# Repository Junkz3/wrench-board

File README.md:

<p align="center">
  <strong>English</strong> ·
  <a href="README.fr.md">Français</a> ·
  <a href="README.zh.md">中文</a> ·
  <a href="README.hi.md">हिन्दी</a> ·
  <a href="README.pt-BR.md">Português</a>
</p>

# Wrench Board

<p align="center">

</p>

> Agent-native diagnostic workbench for board-level electronics repair,
> powered by Claude Opus 4.8. **Right-to-repair, built in the open, by the
> people who actually do the repairs.**

🥈 **2nd place** at Anthropic's *Build with Opus 4.7* hackathon, April 2026.

**📺 Demo video (3 min):** https://youtu.be/OZ2D_p82z6w

**Try it online:** [open a boardview in the browser, free](https://wrenchboard.cloud/boardview-viewer). No account, no install: `.brd`, `.fz`, `.tvw`, `.pcb` and more, parsed natively.

## What it is

Tens of millions of tonnes of electronics end up as e-waste every year. A
large share of that is recoverable at the board level: a dead capacitor, a
blown diode, a bad PMIC, but only a microsoldering technician can find and
fix it. We are the **last mile** of repair before the landfill, and there
are not many of us.

Wrench Board is a senior microsoldering teammate built for that last mile.
For the seasoned tech, it's a second pair of eyes that never gets tired.
For the apprentice, it's a senior teammate who explains the boot sequence
the tenth time, in their language, with their tools, without judgment. It ingests a schematic PDF and a
boardview, builds a per-device knowledge pack in two minutes, and runs an
Opus 4.8 diagnostic agent that pilots the board visually (highlights
pins, traces nets, simulates failures) while the technician keeps the
iron in their hand.

It is device-agnostic. Feed it a schematic and a boardview and it works
the same on iPhone and MacBook logic boards, Android and Samsung phones,
game console motherboards, laptops, and single-board computers. Anything
with a schematic and a boardview is fair game.

The bet is **precision over magic**. The agent is not allowed to invent a
reference designator. Every refdes it utters originates from a tool lookup,
and a server-side sanitizer wraps any token it cannot verify *before* the
text reaches the screen. The deterministic engines underneath produce
verifiable causal chains, not vibes.

## Why it exists

I've been a microsoldering technician for three years. For most of that
time, I sent screenshots to Claude one at a time, manually, and pasted the
answer into a paper notebook. I built the workbench I needed.

## How it works

Four orthogonal workflows feed a single on-disk corpus per device under
`memory/{slug}/`:

- **Knowledge Factory**: four Claude personas (Scout, Registry, Writers,
  Auditor) build a verified repair pack from a device label in ~2 minutes.
  The three Writers (Cartographe / Clinicien / Lexicographe) run in
  parallel and share a cache-warmed prefix to amortize the long shared
  input across writers.
- **Schematic Ingestion**: Opus 4.8 vision compiles a PDF schematic, page
  by page, into a queryable `ElectricalGraph`: nets classified, boot
  sequence inferred, quality report attached.
- **Diagnostic Agent**: an Anthropic Managed Agent per device, with a
  four-store layered memory (`global-patterns`, `global-playbooks`,
  `device-{slug}`, `repair-{repair_id}`), pilots the boardview through 17
  `bv_*` tools and queries the pack, schematic graph, measurements,
  validations and technician profile through 27 more: 44 custom tools
  declared in `api/agent/manifest.py`. The agent never fabricates a
  refdes: tool discipline plus a post-hoc sanitizer.
- **microsolder-evolve**: four overnight search loops, one
  per surface: the deterministic simulator + hypothesize engines
  (`sim`), the schematic compiler (`pipeline`), the schematic vision
  pass (`pipeline-vision`), and the diagnostic agent itself (`agent`).
  Each loop proposes patches against an oracle benchmark and either
  keeps them (`evolve:`-prefixed commit) or reverts. The loops have
  been running and shipping improvements while I work on other things.

### Files + Vision: the agent can ask to see

A microsoldering diagnosis lives or dies on what the probe is touching
*right now*, and a chat box can't carry that. The technician plugs a USB
microscope or webcam into the workbench and the agent requests a frame on
demand through the `cam_capture` tool, reads the image, and feeds it back
into its reasoning. The technician can also drop a macro shot or a close-up
of a suspect chip into the chat at any time. Captures and uploads are
persisted under the repair so a session can be replayed end-to-end:
words, decisions, and the actual photographs the agent looked at.

This closes the loop the screenshot-pasting workflow never could: the
agent stops *guessing* what the board looks like and starts *seeing* it,
on the technician's cue, on the technician's optics.

## Under the hood

- **Backend**: Python 3.11+ / FastAPI / native WebSocket / Pydantic v2 /
  pdfplumber. No build step, no bundler.
- **Frontend**: vanilla HTML + CSS + JS, OKLCH design tokens, D3 v7 for the
  knowledge graph and Three.js r128 (WebGL) for the boardview. Inline SVG
  icons. No framework.
- **Models**: Claude Opus 4.8 (heavy pipeline writers, schematic vision,
  `deep` diagnostic tier), Claude Sonnet 4.6 (Scout, Registry, Mapper,
  Lexicographe, `normal` tier), Claude Haiku 4.5 (intent classifier, phase
  narrator, coverage gate, `fast` tier).
- **Memory**: per-device Anthropic Managed Agents memory stores. The
  agent self-orients across sessions by reading its own scribe notebook
  (`state.md`, `decisions/`, `measurements/`, `open_questions.md`)
  instead of relying on an LLM-generated resume.
- **Boardview**: 16 parsers in `api/board/parser/`, dispatched
  by extension: KiCad `.kicad_pcb`, OpenBoardView Test_Link `.brd`,
  KiCad-boardview BRD2, plus `.asc` `.bdv` `.bv` `.bvr` `.cad` `.cst`
  `.f2b` `.fz` `.gr` `.pcb` `.tvw`. Adding a format = one new file.
- **Tests**: 2 600+ fast tests (~1 min) plus a `@slow` accuracy-gate suite,
  including 10 deterministic invariants on the simulator + hypothesize
  engines and frozen-oracle gates.
- **Tooling**: `make doctor` runs 8 local health checks (env, packs,
  parsers, camera) for atelier deployment. `make eval-all` orchestrates
  the four eval surfaces (simulator, pipeline, vision, agent) with
  cross-skill regression detection. `make tools-inventory` writes a
  local agent-manifest index for offline review.
- **Anti-hallucination**: defense in depth, two layers. (1) Tools return
  `{found: false, closest_matches: [...]}` for unknown refdes; the system
  prompt instructs the agent to pick from suggestions or ask the user.
  (2) `api/agent/sanitize.py` scans every outbound text for refdes-shaped
  tokens (`\b[A-Z]{1,3}\d{1,4}\b`) and wraps any unverified match as
  `⟨?U999⟩` before it reaches the technician.

Two pure-sync deterministic engines (`simulator.py`, `hypothesize.py`) sit
at the core of the diagnostic stack. The simulator advances phase-by-phase
over a boot sequence and emits a timeline of dead rails, dead components,
and the cause of blocking per phase. The hypothesizer takes a partial
observation and enumerates 1- and 2-fault refdes-kill candidates that
explain it, ranked by F1 against the observation. Neither calls an LLM at
runtime.

The diagnostic agent has two interchangeable runtimes: **managed** via
Anthropic Managed Agents, **direct** via the Messages API. Managed is the
default and the production path; direct serves as a fallback when the MA
beta is unavailable and as an on-disk inspection harness during
development. The WebSocket protocol is identical so the frontend doesn't
know which one is running.

## Roadmap: Community Evolution Loop

Wrench Board runs locally. Each technician's instance can improve its
deterministic simulator against their own field cases. When the evolve
loop discovers a rule that holds up, it surfaces a candidate pull request
to the upstream repo. Right-to-repair, built in the open, by the people
who actually do the repairs.

## Quickstart

```bash
git clone https://github.com/Junkz3/wrench-board
cd wrench-board
make install          # create .venv and install deps (incl. [dev])
cp .env.example .env  # then fill in ANTHROPIC_API_KEY
make run              # uvicorn --reload on http://localhost:8000
```

On the first `make run` in Managed Agents mode (default), the start
script prints a one-screen warning describing what it is about to create
on your Anthropic account (1 environment + 3 tier-scoped agents, idle,
no cost until used) and waits 5 seconds for Ctrl+C before bootstrapping.
The IDs land in `managed_ids.json` (gitignored) and subsequent runs go
straight to uvicorn.

Fallback to direct mode if the Managed Agents beta is unavailable on
your account, no bootstrap, plain `messages.create` tool loop:

```bash
make demo-fallback
# or: DIAGNOSTIC_MODE=direct make run
```

## License & credits

Source-available under a proprietary license. See [`LICENSE`](LICENSE).
Free for personal evaluation, study, and local use. **Independent
electronics repair professionals may also use it as an internal tool
when servicing their own clients** (commercial remuneration OK), with
no separate licence needed. Redistribution, hosted SaaS deployment,
sublicensing, and any use for training competing AI / ML models still
require written permission (contact: alexis@repairmind.co.uk).
Dependencies are MIT / Apache 2.0 / BSD only. The MNT Reform motherboard
used as the canonical test target is CERN-OHL-S-2.0. Built solo at
Repair Valley, an independent electronics repair workshop.

## Contributing

Wrench Board is open to contributors who care about right-to-repair.
Field reports, new boardview parsers, simulator rules: open an issue or
a PR.

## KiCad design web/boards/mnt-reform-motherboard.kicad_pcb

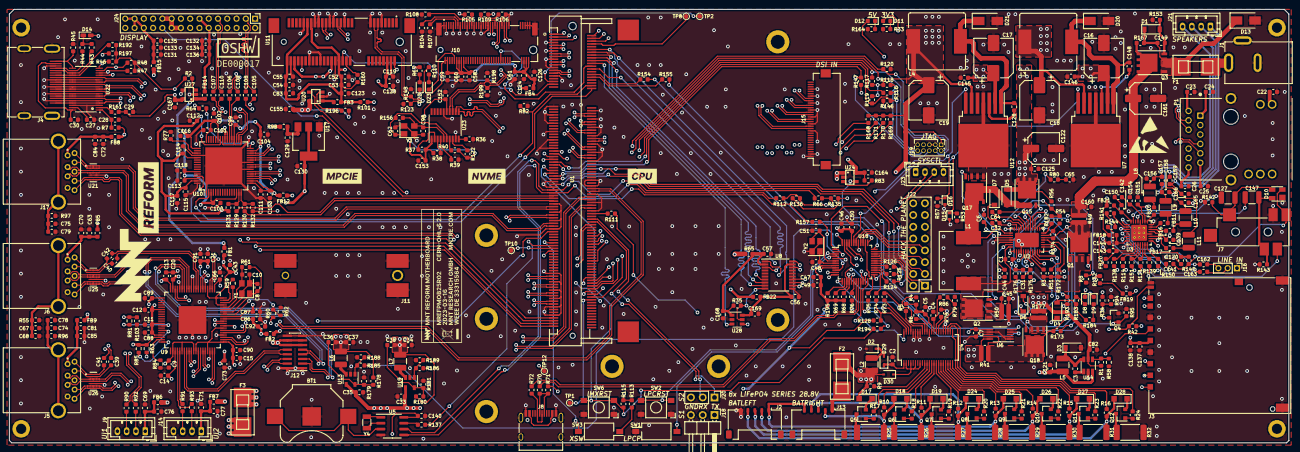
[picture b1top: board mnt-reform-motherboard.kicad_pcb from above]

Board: 6 copper layers, 276.0 x 93.5 mm, 505 parts (0 on the bottom side), 450 nets.

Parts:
BT1: CR1220; BatteryHolder_Keystone_3000_1x12mm
C1, C4, C5, C32, C73, C87, C89, C100, C111, C114, C129, C130, C141, C145, C146, C162, C163: 1uF; C_0603_1608Metric
C2, C7, C9, C11, C12, C13, C14, C15, C20, C21, C22, C23, C24, C25, C26, C27, C28, C29, C30, C39, C40, C41, C42, C43, C49, C50, C53, C54, C55, C56, C57, C59, C60, C61, C66, C67, C70, C74, C75, C76, C77, C84, C85, C86, C88, C90, C101, C103, C105, C106, C107, C108, C109, C110, C113, C115, C118, C119, C135, C136, C138, C140, C142, C143, C144, C149, C154, C156, C158, C165, C166, C168, C169: 0.1uF; C_0603_1608Metric
C3, C31: 0.33uF; C_0603_1608Metric
C6, C33, C35, C139, C151, C170: 4.7uF; C_0603_1608Metric
C8, C10, C48, C51, C62, C98: 18pF; C_0603_1608Metric
C16, C17: 100uF; CP_Elec_8x10
C18, C19: 220uF; CP_Elec_8x10
C34, C37, C46, C47, C63, C69, C71, C72, C81, C91, C92, C99, C112, C120, C131, C132, C133, C134, C137, C150, C155, C164, C167: 10uF; C_0603_1608Metric
C36, C38: 6.8pF; C_0603_1608Metric
C44, C82, C125, C160: 2.2uF; C_0603_1608Metric
C45: 0.033uF; C_0603_1608Metric
C52, C58, C102, C104, C116, C117, C128, C148, C152, C153: 10nF; C_0603_1608Metric
C64, C68, C78, C79: 2nF; C_0603_1608Metric
C65: 680pF; C_0603_1608Metric
C83, C121, C123, C124, C126: 47uF; C_0603_1608Metric
C122, C161: 100uF; CP_Elec_6.3x7.7
C127, C147: 220uF; C_1210_3225Metric
C157, C159: 470nF; C_0603_1608Metric
D1: BZT52C10; D_SOD-123
D2, D29, D30: BAT46WJ,115; D_SOD-323
D3, D4, D6: SBR0560S1; D_SOD-123
D5: NOSTUFF; D_SOD-123
D7: BZT52C6V2-7-F; D_SOD-123
D8: LEDCHG1; LED_0603_1608Metric
D9: LEDCHG2; LED_0603_1608Metric
D10: SP0503BAHT; SOT-143
D11: LED3V; LED_0603_1608Metric
D12: LED5V; LED_0603_1608Metric
D13: SMAJ36CA-E3/5A; D_SMA
D14: SD0603S040S0R2; D_0603_1608Metric_Castellated
D15, D16: BZX584C3V3-G3-08; D_SOD-523
D17, D18, D19, D24, D25, D26, D27, D28: PMEG60T10ELR; Nexperia_CFP3_SOD-123W
D20, D21: SK54A-LTP; D_SMA
D22: LED_WLAN1; LED_0603_1608Metric
D23: LED_NVME; LED_0603_1608Metric
F1, F2, F3: 0157004.DR; fuse_smf
FB1, FB2, FB5, FB6, FB7, FB8, FB9: 220@100MHz 1.4A; L_0603_1608Metric
FB3, FB4, FB10, FB11, FB12, FB14, FB15, FB16, FB17, FB18, FB19, FB20, FB21, FB22: 100@100MHz 3A; L_0603_1608Metric
H1: NGFF-Mount1; WA-SMSI-M2
H2: NGFF-Mount2; WA-SMSI-M2
H3: NGFF-Mount3; WA-SMSI-M2
H5, H6, H7, H8: MountingHole_Pad; MountingHole_2.2mm_M2_DIN965_Pad
H9: OSHWA_DE17; oshwa-de17
H10: LOGO_REFORM; mntreform
H11: LABEL_MPCIE1; mpcie
H12: LABEL_MPCIE2; nvme
H13: LABEL_CPU; cpu
H14: BADGE; reform2-motherboard-badge
H15: NOTOUCH; ESD-Logo_8.9x8mm_SilkScreen
H22, H24, H25, H27: MountingHole_Pad; WA-SMSI-M2
J1: Jack-DC; SWC_RAPC712X
J2: BATCON2; Molex_Pico-Lock_504050-0591_1x05-1MP_P1.50mm_Horizontal
J3: SD_Card; TE_1775059-1
J4: HDMI_A; HDMI-685119134923
J5, J6, J17: USB3_A; 692121030100
J7: SJ-43516-SMT
J8: USB_C_Receptacle_USB2.0; USB_C_Receptacle_HRO_TYPE-C-31-M-12
J9: USB_INT1; JST_PH_B4B-PH-K_1x04_P2.00mm_Vertical
J10: 1-2199230-6; TE_1-2199230-6
J11: 48099-5701; MOLEX_48099-5701
J12: Conn_02x08_Odd_Even; PinHeader_2x08_P1.00mm_Vertical_SMD
J13: BATCON1; Molex_Pico-Lock_504050-0591_1x05-1MP_P1.50mm_Horizontal
J14: USB_INT2; JST_PH_B4B-PH-K_1x04_P2.00mm_Vertical
J15: Conn_01x33; Hirose_FH12-33S-0.5SH_1x33-1MP_P0.50mm_Horizontal
J16: LINE_IN; PinHeader_1x03_P2.00mm_Vertical
J18: Conn_01x03_Male; PinHeader_1x03_P2.54mm_Horizontal
J19: JTAG; PinHeader_2x05_P1.27mm_Vertical
J20: Conn_01x03_Male; PinHeader_1x03_P2.54mm_Vertical
J21: Conn_01x04; JST_PH_B4B-PH-K_1x04_P2.00mm_Vertical
J22: LPC_IO; PinHeader_2x08_P2.54mm_Vertical
J23: KDBSYSCTL; JST_PH_B4B-PH-K_1x04_P2.00mm_Vertical
J24: EDP_HEADER; PinHeader_2x15_P2.00mm_Vertical
L1: 22uH 5A; L_12x12mm_H6mm
L2: IMC1210ER100K; L_1210_3225Metric
L3, L4: 68uH; L_Bourns_SRR1210A
L5: 10uH; L_1210_3225Metric
L6, L7: 2.2uH; L_1210_3225Metric
L8, L9, L10, L11: 15uH; L_1210_3225Metric
P1: J0G-0003NL; PULSE_J0G-0003NL
Q1, Q2, Q15, Q17: Si7850DP; PowerPAK_SO-8_Single_8Pads
Q3, Q18: Si7461DP; PowerPAK_SO-8_Single_8Pads
Q4: PMV50ENEAR; SOT-23
Q5, Q6, Q7, Q8, Q9, Q10, Q11, Q12: PMV50EPEAR; SOT-23
R1, R7, R39, R51, R65, R73, R74, R75, R76, R77, R78, R81, R98, R101, R104, R105, R106, R107, R108, R109, R111, R116, R124, R125, R126, R129, R130, R137, R141, R146, R147, R152, R154, R155, R157, R182, R185, R186, R193, R194: 0; R_0603_1608Metric
R2, R9, R45, R54, R62, R63, R83, R84, R85, R95, R113, R115, R117, R118, R119, R128, R161, R168, R169, R170, R171, R172, R196: 10k; R_0603_1608Metric
R3, R8, R46, R56, R58, R82, R86, R94, R103, R120, R160, R178, R179, R181, R188, R189: 100k; R_0603_1608Metric
R4, R5, R6, R55, R61, R96, R97, R153, R156: 1M; R_0603_1608Metric
R10, R11, R12, R13, R14, R15, R16, R175, R176: 100; R_0603_1608Metric
R17, R18, R19, R20, R21, R22, R23, R24: 3.3k; R_0603_1608Metric
R25, R26, R27, R28, R29, R30, R31, R32: 15; R_2512_6332Metric
R33, R43, R44, R68, R69, R131, R132, R135, R136, R164, R174: 4.7k; R_0603_1608Metric
R34, R180: 150k; R_0603_1608Metric
R35, R37, R38, R40, R42, R71, R122, R195: 1.5k; R_0603_1608Metric
R36: 475; R_0603_1608Metric
R41, R177: 0.02; R_0612_1632Metric
R47, R48, R80, R142, R143, R144, R197: 47k; R_0603_1608Metric
R49, R50: 0.01; R_0612_1632Metric
R53, R57, R64: 51k; R_0603_1608Metric
R59: 9.09K 1%; R_0603_1608Metric
R60: 90.9K 1%; R_0603_1608Metric
R66, R112: 220; R_0603_1608Metric
R67, R110, R183, R184: 1k; R_0603_1608Metric
R70, R72, R114, R121, R138, R139, R150, R151: 33; R_0603_1608Metric
R79: 100k NTC; R_0603_1608Metric
R90, R91, R92, R93: 27; R_0603_1608Metric
R123, R148, R198, R199: 49.9; R_0603_1608Metric
R140: 680; R_0603_1608Metric
R167: 62; R_0603_1608Metric
R173: 49.9k; R_0603_1608Metric
R192: 27k; R_0603_1608Metric
SW1, SW3: SW_DIP_x01; SW_DIP_SPSTx01_Slide_Omron_A6S-110x_W8.9mm_P2.54mm
SW2, SW6: SW_Push; UK-B0206-G3.8-250-JZ
TP1: IMX_PWM4; TestPoint_Pad_D1.0mm
TP2: T_OTG; TestPoint_Pad_D1.0mm
TP8: T_PMIC_ON_REQ; TestPoint_Pad_D1.0mm
TP10: T_M4_NMI; TestPoint_Pad_D1.0mm
TP12: SAI2_RXC; TestPoint_Pad_D1.0mm
U1: Nitrogen8M_SOM; TE_1473149-4
U2: LTC4020EUHFPBF; QFN-38-1EP_5x7mm_P0.5mm_EP3.15x5.15mm
U3: WM8960; QFN-32-1EP_5x5mm_P0.5mm_EP3.45x3.45mm_ThermalVias
U4: LTC6803-4; SSOP-44_5.3x12.8mm_P0.5mm
U5: PCF8523T; SOIC-8_3.9x4.9mm_P1.27mm
U6: INA233; VSSOP-10_3x3mm_P0.5mm
U7: LM2677SX-5; TO-263-7_TabPin8
U8: TXS0108EPW; TSSOP-20_4.4x6.5mm_P0.65mm
U9: TUSB8040PFP; QFP50P1400X1400X120-81N
U10: SN65DSI86IPAPQ1; HTQFP-64-1EP_10x10mm_P0.5mm_EP8x8mm
U11: 679105700; MOLEX_67910-5700
U12: LM2677SX-3.3; TO-263-7_TabPin8
U13, U19: TLV62568DBV; SOT-23-5
U14: LMR16006YQ3; TSOT-23-6
U17: TLV1117-18; SOT-223
U18: LPC11U24FBD48-301; LQFP-48_7x7mm_P0.5mm
U20, U24, U27: AP22815; TSOT-25
U21, U25, U26: SP3012-06UTG; SON50P350X135X55-14N
U22: TPD12S521; TSSOP50P640X120-38N
U23: IDT5V41066; TSSOP-20_4.4x6.5mm_P0.65mm
U28: SN74AVC1T45; SOT-23-6
Y1: 24MHz; Crystal_SMD_Abracon_ABM8G-4Pin_3.2x2.5mm
Y2: 12MHz; Crystal_SMD_Abracon_ABM8G-4Pin_3.2x2.5mm
Y3: 25MHz; Crystal_SMD_Abracon_ABM8G-4Pin_3.2x2.5mm
Y4: 32.768 kHz; Crystal_SMD_3215-2Pin_3.2x1.5mm

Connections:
1V2_PWR_EN: R185.1, U18.2 (PIO1_19)
3V3_PWR_AUX: FB1.1, FB14.1, R98.2, U27.1 (OUT)
3V3_PWR_EN: D16.1 (K), R57.2, U12.7 (ON/~OFF), U18.48 (PIO1_16)
5V_PWR_EN: D15.1 (K), R53.2, U7.7 (ON/~OFF), U18.43 (PIO1_15)
30V_GATE: C16.1, C17.1, C82.2, C122.1, C125.1, C145.2, C146.2, D5.1 (K), Q15.5 (D), Q15.6 (D), Q15.7 (D), Q15.8 (D), R1.2, R56.1, R175.1, R177.1, U7.2 (VIN), U12.2 (VIN), U14.5 (VIN)
+1V2: C36.1, C37.1, FB2.1, FB12.1, L6.2, R178.1
+1V5: C34.1, C38.1, C119.1, C120.1, L7.2, R180.1, U11.6 (+1.5V), U11.28 (+1.5V), U11.48 (+1.5V)
+1V8: C112.1, C114.1, C115.1, C117.1, C130.1, R65.2, R131.2, R132.2, U10.42 (VPLL), U10.53 (VCCIO), U10.63 (VCCIO), U17.2 (VO)
+3V3: C19.1, C22.1, C29.1, C155.1, C167.1, D11.2 (A), FB4.1, FB18.1, FB20.1, FB21.1, FB22.1, J19.1 (VTref), L4.2, P1.14 (YEL+), P1.16 (COM+), R2.2, R46.2, R47.2, R48.2, R113.2, R115.1, R117.1, R118.1, R119.1, R135.1, R136.1, R161.1, R168.1, R169.2, R170.2, R171.2, R192.1, R196.2, R197.2, U12.6 (FB), U20.5 (IN), U27.5 (IN)
+5V: C18.1, C33.1, C35.1, C164.1, D12.2 (A), L3.2, R83.2, U1.1 (5V), U1.2 (5V), U1.3 (5V), U1.4 (5V), U1.5 (5V), U1.6 (5V), U7.6 (FB), U13.4 (VIN), U19.4 (VIN), U24.5 (IN)
/Reform 2 Display/EDAUXN: C107.2, U10.35 (AUXN)
/Reform 2 Display/EDAUXP: C110.2, U10.34 (AUXP)
/Reform 2 Display/EDP_BL_VCC: C131.1, C133.1, C135.1, FB15.2, J24.26, J24.27, J24.28, J24.29
/Reform 2 Display/EDP_HPD: J24.17, R64.1
/Reform 2 Display/EDP_LCD_VCC: C132.1, C134.1, C136.1, FB14.2, J24.12, J24.13
/Reform 2 Display/ML0N: C106.2, U10.38 (ML0N)
/Reform 2 Display/ML0P: C109.2, U10.37 (ML0P)
/Reform 2 Display/ML1N: C105.2, U10.40 (ML1N)
/Reform 2 Display/ML1P: C108.2, U10.39 (ML1P)
/Reform 2 PCIe/PCICLKGEN_XI: C98.1, R156.2, U23.5 (X1), Y3.3
/Reform 2 PCIe/PCICLKGEN_XO: C62.1, R156.1, U23.6 (X2), Y3.1
/Reform 2 PCIe/RCLKC_N: J10.53, R199.2, U23.13 (CLKC_N)
/Reform 2 PCIe/RCLKC_P: J10.55, R198.2, U23.14 (CLKC_P)
/Reform 2 Power/24V_IN: F1.1, J1.1
/Reform 2 Power/CHG_INTVCC: C6.2, D4.2 (A), D6.2 (A), R183.1, R184.1, U2.10 (VIN_REG), U2.34 (INTVCC)
/Reform 2 Power/Reform 2 LPC/LPCUD_N: R72.2, U18.19 (USB_DM)
/Reform 2 Power/Reform 2 LPC/LPCUD_P: R70.2, U18.20 (USB_DP)
/Reform 2 Power/Reform 2 LPC/LPC_AD5: J22.7, U18.40 (PIO0_16)
/Reform 2 Power/Reform 2 LPC/LPC_AD7: J22.10, U18.42 (PIO0_23)
/Reform 2 Power/Reform 2 LPC/LPC_MISO0: R124.1, U18.27 (PIO0_8)
/Reform 2 Power/Reform 2 LPC/LPC_MISO1a: J22.2, U18.30 (PIO0_22)
/Reform 2 Power/Reform 2 LPC/LPC_MISO1b: R74.2, U18.26 (PIO1_21)
/Reform 2 Power/Reform 2 LPC/LPC_MOSI0: R125.1, U18.28 (PIO0_9)
/Reform 2 Power/Reform 2 LPC/LPC_MOSI1a: J22.14, U18.17 (PIO0_21)
/Reform 2 Power/Reform 2 LPC/LPC_MOSI1b: R75.2, U18.38 (PIO1_22)
/Reform 2 Power/Reform 2 LPC/LPC_RXDa: J22.12, U18.46 (PIO0_18)
/Reform 2 Power/Reform 2 LPC/LPC_RXDc: J23.3, U18.11 (PIO1_26)
/Reform 2 Power/Reform 2 LPC/LPC_SCK0a: R126.1, U18.29 (PIO0_10)
/Reform 2 Power/Reform 2 LPC/LPC_SCK0b: J22.1, U18.31 (PIO1_29)
/Reform 2 Power/Reform 2 LPC/LPC_SCK1b: R73.2, U18.13 (PIO1_20)
/Reform 2 Power/Reform 2 LPC/LPC_SCLKa: J22.9, U18.45 (PIO0_17)
/Reform 2 Power/Reform 2 LPC/LPC_SCLKc: R194.2, U18.24 (PIO1_28)
/Reform 2 Power/Reform 2 LPC/LPC_SSEL0: R157.1, U18.10 (PIO0_2)
/Reform 2 Power/Reform 2 LPC/LPC_SSEL1: R76.2, U18.18 (PIO1_23)
/Reform 2 Power/Reform 2 LPC/LPC_SWDIO: J22.8, U18.39 (PIO0_15)
/Reform 2 Power/Reform 2 LPC/LPC_TDI: J22.4, U18.32 (PIO0_11)
/Reform 2 Power/Reform 2 LPC/LPC_TDO: J22.6, U18.34 (PIO0_13)
/Reform 2 Power/Reform 2 LPC/LPC_TMS: J22.3, U18.33 (PIO0_12)
/Reform 2 Power/Reform 2 LPC/LPC_TXDa: J22.11, U18.47 (PIO0_19)
/Reform 2 Power/Reform 2 LPC/LPC_TXDc: J23.2, U18.12 (PIO1_27)
/Reform 2 Power/Reform 2 LPC/LPC_UFTOGG: SW1.2, U18.4 (PIO0_1)
/Reform 2 Power/Reform 2 LPC/LPC_UVBUS: R195.2, U18.14 (PIO0_3)
/Reform 2 Power/Reform 2 LPC/LPC_~RESET: SW2.2, U18.3 (PIO0_0)
/Reform 2 Power/Reform 2 LPC/LPC_~TRST: J22.5, U18.35 (PIO0_14)
/Reform 2 Power/Reform 2 LPC/LPC_~USBCON: J22.13, U18.22 (PIO0_6)
/Reform 2 Power/VIN: C44.2, C160.1, C161.1, Q3.5 (D), Q3.6 (D), Q3.7 (D), Q3.8 (D), R34.2, R49.2, R167.1, U2.7 (SENSVIN), U2.36 (PVIN)
/Reform 2 Power/VREG: C5.1, R4.1, R5.1, R6.1, U4.32 (Vreg)
/Reform 2 USB/USB3_1_SSTXCN: C40.2, J6.8 (SSTX-), U25.2, U25.13
/Reform 2 USB/USB3_1_SSTXCP: C42.2, J6.9 (SSTX+), U25.1, U25.14
/Reform 2 USB/USB3_2_SSTXCN: C39.2, J5.8 (SSTX-), U26.2, U26.13
/Reform 2 USB/USB3_2_SSTXCP: C41.2, J5.9 (SSTX+), U26.1, U26.14
AUX_PWR_EN: U18.23 (PIO0_7), U27.4 (EN)
BACKLIGHT_EN: J24.22, U1.105 (GPIO1_IO10)
BACKLIGHT_PWM: J24.23, U1.164 (SPDIF_RX/PWM2)
BAT1+: F2.2, J13.1
BAT1FUSED: D17.2 (A), D30.2 (A), F2.1, L2.1, R9.1, R41.1, U6.10 (Vin+)
BAT2+: D18.2 (A), J13.2, R10.1, R25.1
BAT3+: D19.2 (A), J13.3, R11.1, R26.1
BAT4+: D24.2 (A), J13.4, R12.1, R27.1
BAT5+: D25.2 (A), J2.1, J13.5, R13.1, R28.1
BAT6+: D26.2 (A), J2.2, R14.1, R29.1
BAT7+: D27.2 (A), J2.3, R15.1, R30.1
BAT8+: D28.2 (A), J2.4, R16.1, R31.1
BMON_CS: R76.1, U4.44 (~CSBI)
BMON_SCK: R73.1, U4.41 (SCKI)
BMON_SDI: R75.1, U4.42 (SDI)
BMON_SDO: R74.1, R128.1, U4.43 (SDO)
BOOTCFG_4: R169.1, U1.152 (SAI1_RXD4)
BOOTCFG_10: R168.2, U1.134 (SAI1_TXD2)
BOOTCFG_12: R171.1, U1.138 (SAI1_TXD4)
BOOTCFG_13: R170.1, U1.140 (SAI1_TXD5)
CHGBAT: Q18.5 (D), Q18.6 (D), Q18.7 (D), Q18.8 (D), R41.2, R173.2, U2.20 (BAT), U6.8 (Vbus), U6.9 (Vin-)
CHG_RNG: Q4.1 (G), R95.2, U18.1 (PIO1_25)
CHG_STAT1: D8.1 (K), U2.12 (STAT1)
CHG_STAT2: D9.1 (K), U2.13 (STAT2)
DAC_BCLK: R114.1, U1.170 (SAI2_TXC)
DAC_DIN: R150.1, U1.166 (SAI2_RXD)
DAC_DOUT: R121.1, U1.178 (SAI2_TXD)
DAC_MCLK: R138.2, U1.176 (SAI2_MCLK)
DAC_RXFS: R139.1, U1.168 (SAI2_RXFS)
DAC_SCL: R66.1, U1.101 (I2C3_SCL), U5.6 (SCL)
DAC_SDA: R112.1, U1.103 (I2C3_SDA), U5.5 (SDA)
DAC_TXFS: R151.1, U1.172 (SAI2_TXFS)
DSI_CLK_N: J15.19, U10.25 (DACN)
DSI_CLK_P: J15.20, U10.24 (DACP)
DSI_D0_N: J15.25, U10.20 (DA0N)
DSI_D0_P: J15.26, U10.19 (DA0P)
DSI_D1_N: J15.22, U10.22 (DA1N)
DSI_D1_P: J15.23, U10.21 (DA1P)
DSI_D2_N: J15.16, U10.28 (DA2N)
DSI_D2_P: J15.17, U10.27 (DA2P)
DSI_D3_N: J15.13, U10.30 (DA3N)
DSI_D3_P: J15.14, U10.29 (DA3P)
EDP_AUX_DN: C107.1, J24.10
EDP_AUX_DP: C110.1, J24.9
EDP_IRQ: U1.40 (WL_IRQ), U10.61 (IRQ)
EDP_RESETn: R82.1, U1.38 (WL_EN), U10.2 (~EN)
EDP_SCL: R129.2, U1.107 (I2C4_SCL)
EDP_SDA: R130.2, U1.109 (I2C4_SDA)
EDP_TX0_DN: C106.1, J24.6
EDP_TX0_DP: C109.1, J24.7
EDP_TX1_DN: C105.1, J24.3
EDP_TX1_DP: C108.1, J24.4
ETH0_A+: P1.11 (TDR1+), U1.29 (TRX0_P)
ETH0_A-: P1.10 (TDR1-), U1.27 (TRX0_N)
ETH0_B+: P1.4 (TRD2+), U1.23 (TRX1_P)
ETH0_B-: P1.5 (TRD2-), U1.21 (TRX1_N)
ETH0_C+: P1.3 (TRD3+), U1.17 (TRX2_P)
ETH0_C-: P1.2 (TRD3-), U1.15 (TRX2_N)
ETH0_D+: P1.8 (TRD4+), U1.11 (TRX3_P)
ETH0_D-: P1.9 (TRD4-), U1.9 (TRX3_N)
ETH0_LED_LINK1: J19.6 (SWO/TDO), R147.2, U1.83 (JTAG_TDO)
ETH0_LED_LINK2: J19.10 (~RESET), R119.2, R146.2, U1.81 (JTAG_NTRST)
ETH0_LED_RX: R116.2, U1.79 (JTAG_MOD)
GND: BT1.2 (-), C2.2, C4.2, C5.2, C6.1, C7.2, C9.2, C11.2, C12.2, C13.2, C14.2, C15.2, C16.2, C17.2, C18.2, C19.2, C20.2, C21.2, C22.2, C23.2, C24.2, C25.2, C26.2, C27.1, C28.1, C29.2, C30.2, C33.2, C34.2, C35.2, C37.2, C43.2, C44.1, C45.1, C46.2, C47.2, C48.2, C49.2, C50.2, C51.2, C52.2, C53.2, C54.2, C55.2, C56.2, C57.2, C58.2, C59.2, C60.2, C61.2, C62.2, C63.2, C65.1, C66.2, C67.2, C68.2, C69.2, C70.2, C71.2, C72.2, C73.2, C74.2, C75.2, C76.2, C77.2, C78.2, C79.2, C81.2, C82.1, C83.2, C84.2, C85.2, C86.2, C87.2, C88.2, C89.2, C90.2, C91.2, C92.2, C98.2, C99.2, C100.2, C101.2, C102.2, C103.2, C104.2, C111.2, C112.2, C113.2, C114.2, C115.2, C116.2, C117.2, C118.2, C119.2, C120.2, C121.1, C122.2, C123.2, C124.2, C125.2, C126.2, C129.2, C130.2, C131.2, C132.2, C133.2, C134.2, C135.2, C136.2, C137.2, C138.2, C139.2, C140.1, C142.2, C143.2, C144.1, C145.1, C146.1, C150.2, C151.2, C152.2, C153.2, C154.2, C155.2, C156.2, C158.2, C160.2, C161.2, C164.2, C165.2, C166.2, C167.2, C168.2, C169.2, C170.2, D2.2 (A), D3.2 (A), D10.1 (A), D13.2 (A), D15.2 (A), D16.2 (A), D20.2 (A), D21.2 (A), H1.1, H2.1, H3.1, H5.1, H6.1, H7.1, H8.1, H22.1, H24.1, H25.1, H27.1, J1.2, J1.3, J2.5, J3.3 (VSS), J3.6 (VSS), J3.12 (SHELL1), J3.13 (SHELL2), J4.2 (D2S), J4.5 (D1S), J4.8 (D0S), J4.11 (CKS), J4.17 (GND), J4.SH, J5.4 (GND), J5.7 (DRAIN), J6.4 (GND), J6.7 (DRAIN), J7.4 (RING2), J8.A1 (GND), J8.A12 (GND), J8.B1 (GND), J8.B12 (GND), J8.S1 (SHIELD), J9.4, J10.1, J10.3, J10.9, J10.15, J10.21, J10.27, J10.33, J10.39, J10.45, J10.51, J10.57, J10.71, J10.73, J10.75, J10.S1 (SHIELD), J10.S2 (SHIELD), J11.1, J11.2, J11.3, J11.4, J12.1, J12.2, J12.15, J12.16, J14.4, J15.1, J15.2, J15.12, J15.15, J15.18, J15.21, J15.24, J15.27, J15.30, J16.1, J17.4 (GND), J17.7 (DRAIN), J18.3, J19.3 (GND), J19.5 (GND), J19.9 (GNDDetect), J20.3, J22.16, J23.4, J24.2, J24.5, J24.8, J24.11, J24.18, J24.19, J24.20, J24.21, P1.SH1 (SHIELD), P1.SH2 (SHIELD), Q4.2 (S), Q17.1 (S), Q17.2 (S), Q17.3 (S), R3.1, R8.1, R32.1, R33.1, R36.1, R39.1, R45.2, R50.1, R51.1, R53.1, R55.2, R57.1, R58.2, R62.2, R77.1, R78.2, R79.2, R82.2, R84.2, R94.1, R95.1, R96.2, R97.2, R103.1, R104.2, R105.2, R106.2, R107.2, R108.2, R109.2, R120.2, R123.1, R142.2, R143.2, R148.1, R153.2, R164.1, R172.2, R179.2, R181.2, R188.2, R189.2, R193.1, R198.1, R199.1, SW1.1, SW2.1, SW6.1, U1.7 (GND), U1.13 (GND), U1.19 (GND), U1.25 (GND), U1.31 (GND), U1.41 (GND), U1.44 (GND), U1.47 (GND), U1.50 (GND), U1.53 (GND), U1.56 (GND), U1.59 (GND), U1.62 (GND), U1.65 (GND), U1.68 (GND), U1.71 (GND), U1.74 (GND), U1.80 (GND), U1.94 (GND), U1.95 (GND), U1.98 (GND), U1.99 (GND), U1.104 (GND), U1.110 (GND), U1.111 (GND), U1.116 (GND), U1.117 (GND), U1.123 (GND), U1.129 (GND), U1.161 (GND), U1.167 (GND), U1.173 (GND), U1.179 (GND), U1.185 (GND), U1.191 (GND), U2.3 (SGND_2), U2.4 (SENSGND), U2.29 (SGND_3), U2.35 (PGND), U2.39 (SGND), U3.9 (DGND), U3.20 (SPKGND2), U3.24 (SPKGND1), U3.28 (AGND), U3.33 (GND), U4.26 (C0), U4.27 (V-), U4.33 (TOS), U4.37 (A0), U4.38 (A1), U4.39 (A2), U4.40 (A3), U5.4 (VSS), U6.1 (A1), U6.2 (A0), U6.7 (GND), U7.4 (GND), U7.8 (PAD), U8.11 (GND), U9.64 (GND), U9.81 (GND), U10.1 (ADDR), U10.23 (GND), U10.26 (GND), U10.52 (GND), U10.64 (GND), U10.65 (GND), U11.4 (GND), U11.9 (GND), U11.15 (GND), U11.18 (GND), U11.21 (GND), U11.26 (GND), U11.27 (GND), U11.29 (GND), U11.34 (GND), U11.35 (GND), U11.37 (GND), U11.40 (GND), U11.43 (GND), U11.50 (GND), U12.4 (GND), U12.8 (PAD), U13.2 (GND), U14.2 (GND), U17.1 (GND), U18.5 (VSS), U18.41 (VSS), U19.2 (GND), U20.2 (GND), U21.5, U21.10, U22.3 (GND), U22.5 (TMDS_GND), U22.8 (TMDS_GND), U22.11 (TMDS_GND), U22.14 (TMDS_GND), U22.25 (TMDS_GND), U22.28 (TMDS_GND), U22.31 (TMDS_GND), U22.34 (TMDS_GND), U22.36 (GND), U23.9 (GNDXD), U23.16 (GNDODA), U24.2 (GND), U25.5, U25.10, U26.5, U26.10, U27.2 (GND), U28.2 (GND), Y2.2, Y2.4, Y3.2, Y3.4
HDMI_CEC: R197.1, U1.197 (HDMI_CEC), U22.16 (CE_REMOTE_IN)
HDMI_CLK+: J4.10 (CK+), U1.165 (HDMI_CLK_P), U22.13 (TMDS_CK+), U22.26 (TMDS_CK+)
HDMI_CLK-: J4.12 (CK-), U1.163 (HDMI_CLK_N), U22.15 (TMDS_CK-), U22.24 (TMDS_CK-)
HDMI_D0+: J4.7 (D0+), U1.171 (HDMI_TX0_P), U22.10 (TMDS_D0+), U22.29 (TMDS_D0+)
HDMI_D0-: J4.9 (D0-), U1.169 (HDMI_TX0_N), U22.12 (TMDS_D0-), U22.27 (TMDS_D0-)
HDMI_D1+: J4.4 (D1+), U1.177 (HDMI_TX1_P), U22.7 (TMDS_D1+), U22.32 (TMDS_D1+)
HDMI_D1-: J4.6 (D1-), U1.175 (HDMI_TX1_N), U22.9 (TMDS_D1-), U22.30 (TMDS_D1-)
HDMI_D2+: J4.1 (D2+), U1.183 (HDMI_TX2_P), U22.4 (TMDS_D2+), U22.35 (TMDS_D2+)
HDMI_D2-: J4.3 (D2-), U1.181 (HDMI_TX2_N), U22.6 (TMDS_D2-), U22.33 (TMDS_D2-)
HDMI_HPD: R46.1, U1.199 (HDMI_HPD), U22.19 (HOTPLUG_DET_IN)
HDMI_SCL: R47.1, U1.195 (HDMI_DDC_SCL), U22.17 (DDC_CLK_IN)
HDMI_SDA: R48.1, U1.193 (HDMI_DDC_SDA), U22.18 (DDC_DAT_IN)
IMX_FBOOT: SW3.2, U1.139 (FAST_BOOT)
IMX_JTAG_TCK: J19.4 (SWDCLK/TCK), R120.1, U1.73 (JTAG_TCK)
IMX_JTAG_TDI: J19.8 (NC/TDI), R118.2, U1.75 (JTAG_TDI)
IMX_JTAG_TMS: J19.2 (SWDIO/TMS), R117.2, U1.77 (JTAG_TMS)
IMX_RESETn: R115.2, R194.1, SW6.2, U1.87 (EXT_RESET_N)
IMX_RTC_IRQ: R137.1, U1.141 (RTC_IRQ)
IMX_UART1_RX: J18.2, U1.126 (UART1_RXD)
IMX_UART1_TX: J18.1, U1.128 (UART1_TXD)
IMX_UART2_RX: J20.2, U1.122 (UART2_RXD)
IMX_UART2_TX: J20.1, U1.124 (UART2_TXD)
IMX_WAKE: U1.145 (GPIO1_IO3), U18.21 (PIO1_24)
INA_SCL: R69.2, U6.5 (SCL), U18.15 (PIO0_4)
INA_SDA: R68.2, U6.4 (SDA), U18.16 (PIO0_5)
LPC_MISO: R124.2, U1.93 (ECSPI2_MISO)
LPC_MOSI: R125.2, U1.91 (ECSPI2_MOSI)
LPC_SCK: R126.2, U1.97 (ECSPI2_SCLK)
LPC_SS0: R157.2, U1.89 (ECSPI2_SS0)
LPC_UART2_RX: R154.1, U18.37 (PIO1_14)
LPC_UART2_TX: R155.2, U18.36 (PIO1_13)
LPC_VCC: C7.1, C46.1, C47.1, C49.1, C50.1, C121.2, C140.2, J22.15, J23.1, L5.2, R68.1, R69.1, R71.1, R128.2, R195.1, U5.8 (VDD), U6.6 (VS), U14.3 (FB), U18.8 (VDD), U18.44 (VDD)
unnamed: BT1.1 (+), U5.3 (VBAT)
unnamed: C1.1, D4.1 (K), U2.2 (BST1)
unnamed: C1.2, L1.1, Q1.1 (S), Q1.2 (S), Q1.3 (S), Q2.5 (D), Q2.6 (D), Q2.7 (D), Q2.8 (D), U2.38 (SW1)
unnamed: C2.1, D29.1 (K), U4.1 (V+)
unnamed: C3.1, D3.1 (K), L5.1, U14.6 (SW)
unnamed: C3.2, U14.1 (BOOST)
unnamed: C4.1, R86.2, U4.31 (Vref)
unnamed: C8.1, R61.1, U9.74 (XO), Y1.1
unnamed: C10.1, R61.2, U9.76 (XI), Y1.3
unnamed: C8.2, C10.2, U9.75 (VSSOSC), Y1.2, Y1.4
unnamed: C23.1, P1.7 (TRCT4)
unnamed: C24.1, P1.1 (TRCT3)
unnamed: C25.1, P1.6 (TRCT2)
unnamed: C26.1, P1.12 (TRCT1)
unnamed: C27.2, U22.37 (ESD_BYP)
unnamed: C28.2, R7.1, U22.1 (5V_SUPPLY)
unnamed: C30.1, J4.18 (+5V), U22.38 (5V_OUT)
unnamed: C31.1, R176.2, U2.22 (CSN)
unnamed: C31.2, R175.2, U2.23 (CSP)
unnamed: C32.1, D6.1 (K), D7.1 (K), U2.30 (BST2)
unnamed: C32.2, D5.2 (A), D7.2 (A), L1.2, Q15.1 (S), Q15.2 (S), Q15.3 (S), Q17.5 (D), Q17.6 (D), Q17.7 (D), Q17.8 (D), U2.32 (SW2)
unnamed: C36.2, R178.2, R179.1, U13.5 (FB)
unnamed: C38.2, R180.2, R181.1, U19.5 (FB)
unnamed: C45.2, Q2.1 (S), Q2.2 (S), Q2.3 (S), R50.2, U2.5 (SENSBOT)
unnamed: C48.1, U18.7 (XTALOUT), Y2.1
unnamed: C51.1, U18.6 (XTALIN), Y2.3
unnamed: C63.1, C70.1, FB5.2, J6.1 (VBUS)
unnamed: C64.1, U2.24 (CSOUT)
unnamed: C64.2, U2.27 (ITH)
unnamed: C65.2, R80.1
unnamed: C67.1, C68.1, J6.10 (SHIELD), R55.1
unnamed: C69.1, C76.1, FB6.2, J9.1
unnamed: C71.1, C77.1, FB7.2, J14.1
unnamed: C72.1, C84.1, FB8.2, J17.1 (VBUS)
unnamed: C74.1, C78.1, J5.10 (SHIELD), R96.1
unnamed: C75.1, C79.1, J17.10 (SHIELD), R97.1
unnamed: C81.1, C85.1, FB9.2, J5.1 (VBUS)
unnamed: C99.1, C100.1, C101.1, C102.1, C103.1, C104.1, C111.1, C113.1, C116.1, C118.1, FB12.2, U10.3 (VCCA), U10.14 (VCCA), U10.17 (VCC), U10.18 (VCCA), U10.31 (VCCA), U10.33 (VCC), U10.36 (VCCA), U10.41 (VCCA), U10.43 (VCCA), U10.48 (VCCA), U10.49 (VCC), U10.59 (VCC), U10.62 (VCC)
unnamed: C52.1, C53.1, C54.1, C55.1, C83.1, C123.1, FB3.2, R67.1, R101.2, R160.1, U11.2 (+3.3Vaux), U11.24 (+3.3Vaux), U11.39 (+3.3Aux), U11.41 (+3.3Aux), U11.52 (+3.3Vaux)
unnamed: C58.1, C59.1, C60.1, C61.1, C124.1, C126.1, FB4.2, J10.2, J10.4, J10.12, J10.14, J10.16, J10.18, J10.70, J10.72, J10.74, R110.1
unnamed: C127.1, D10.3 (K), J7.2 (TIP), R142.1
unnamed: C127.2, U3.31 (HP_L)
unnamed: C128.1, D21.1 (K), L4.1, U12.1 (VSW)
unnamed: C128.2, U12.3 (CB)
unnamed: C129.1, R98.1, U17.3 (VI)
unnamed: C56.1, C137.1, C138.1, C169.1, FB22.2, J3.4 (VDD), R42.1, U8.19 (VCCB), U28.6 (VCCB)
unnamed: C139.1, C151.1, FB19.2, U3.21 (SPKVDD2), U3.26 (SPKVDD1)
unnamed: C141.1, D10.2 (K), J7.1 (SLEEVE), R140.2
unnamed: C141.2, U3.4 (LINPUT1)
unnamed: C142.1, FB21.2, U3.32 (AVDD)
unnamed: C143.1, FB20.2, R144.1, U3.10 (DBVDD)
unnamed: C144.2, FB18.2, U3.8 (DCVDD)
unnamed: C147.1, D10.4 (K), J7.3 (RING1), R143.1
unnamed: C147.2, U3.29 (HP_R)
unnamed: C148.1, D20.1 (K), L3.1, U7.1 (VSW)
unnamed: C148.2, U7.3 (CB)
unnamed: C149.1, D1.1 (K), D13.1 (K), F1.2, Q3.1 (S), Q3.2 (S), Q3.3 (S), R167.2
unnamed: C149.2, D1.2 (A), Q3.4 (G), R153.1
unnamed: C150.1, C154.1, U3.27 (VMID)
unnamed: C152.1, C153.1, R37.1, R38.1, R40.1, R101.1, R122.1, U23.1 (VDDXD), U23.15 (VDDODA)
unnamed: C156.1, C157.1, J21.4, L8.2
unnamed: C157.2, C158.1, J21.3, L9.2
unnamed: C159.1, C165.1, J21.2, L10.2
unnamed: C159.2, C166.1, J21.1, L11.2
unnamed: C162.1, U3.3 (LINPUT2)
unnamed: C162.2, J16.3
unnamed: C163.1, U3.6 (RINPUT2)
unnamed: C163.2, J16.2
unnamed: C57.1, C168.1, R35.1, R65.1, U8.2 (VCCA), U28.1 (VCCA)
unnamed: C170.1, R140.1, U3.1 (MICBIAS)
unnamed: D2.1 (K), D29.2 (A), L2.2
unnamed: D8.2 (A), R183.2
unnamed: D9.2 (A), R184.2
unnamed: D11.1 (K), R33.2
unnamed: D12.1 (K), R164.2
unnamed: D14.1 (K), R43.1, R44.1
unnamed: D17.1 (K), Q5.2 (S)
unnamed: D18.1 (K), Q6.2 (S)
unnamed: D19.1 (K), Q7.2 (S)
unnamed: D22.1 (K), U11.44 (~LED_WLAN)
unnamed: D22.2 (A), R67.2
unnamed: D23.1 (K), J10.10
unnamed: D23.2 (A), R110.2
unnamed: D24.1 (K), Q8.2 (S)
unnamed: D25.1 (K), Q9.2 (S)
unnamed: D26.1 (K), Q10.2 (S)
unnamed: D27.1 (K), Q11.2 (S)
unnamed: D28.1 (K), Q12.2 (S)
unnamed: D30.1 (K), U4.2 (C12), U4.4 (C11), U4.6 (C10), U4.8 (C9)
unnamed: FB3.1, U20.1 (OUT)
unnamed: FB10.1, U3.25 (SPK_LP)
unnamed: FB10.2, L8.1
unnamed: FB11.1, U3.23 (SPK_LN)
unnamed: FB11.2, L9.1
unnamed: FB16.1, U3.22 (SPK_RP)
unnamed: FB16.2, L10.1
unnamed: FB17.1, U3.19 (SPK_RN)
unnamed: FB17.2, L11.1
unnamed: FB19.1, R152.2
unnamed: J3.1 (CD/DAT3), U8.13 (B7)
unnamed: J3.2 (CMD), U8.14 (B6)
unnamed: J3.5 (CLK), U28.4 (B)
unnamed: J3.7 (DAT0), U8.18 (B2)
unnamed: J3.8 (DAT1), U8.20 (B1)
unnamed: J3.9 (DAT2), U8.12 (B8)
unnamed: J4.13 (CEC), R192.2, U22.23 (CE_REMOTE_OUT)
unnamed: J4.15 (SCL), R43.2, U22.22 (DDC_CLK_OUT)
unnamed: J4.16 (SDA), R44.2, U22.21 (DDC_DAT_OUT)
unnamed: J4.19 (HPD), R45.1, U22.20 (HOTPLUG_DET_OUT)
unnamed: J7.6 (RING_SWITCH), R141.1, R144.2
unnamed: J8.A6 (D+), J8.B6 (D+), R70.1, R71.2
unnamed: J8.A7 (D-), J8.B7 (D-), R72.1
unnamed: J9.2, R92.2
unnamed: J9.3, R90.2
unnamed: J10.11, R107.1
unnamed: J10.13, R104.1
unnamed: J10.23, R108.1
unnamed: J10.25, R105.1
unnamed: J10.35, R109.1
unnamed: J10.37, R106.1
unnamed: J14.2, R93.2
unnamed: J14.3, R91.2
unnamed: L6.1, U13.3 (SW)
unnamed: L7.1, U19.3 (SW)
unnamed: P1.13 (YEL-), R116.1
unnamed: P1.15 (ORN-), R146.1
unnamed: P1.17 (GRN-), R147.1
unnamed: Q1.4 (G), U2.1 (TG1)
unnamed: Q1.5 (D), Q1.6 (D), Q1.7 (D), Q1.8 (D), R49.1, U2.6 (SENSTOP)
unnamed: Q2.4 (G), U2.37 (BG1)
unnamed: Q4.3 (D), R172.1, U2.16 (NTC)
unnamed: Q5.1 (G), R17.1
unnamed: Q5.3 (D), R25.2
unnamed: Q6.1 (G), R18.1
unnamed: Q6.3 (D), R26.2
unnamed: Q7.1 (G), R19.1
unnamed: Q7.3 (D), R27.2
unnamed: Q8.1 (G), R20.1
unnamed: Q8.3 (D), R28.2
unnamed: Q9.1 (G), R21.1
unnamed: Q9.3 (D), R29.2
unnamed: Q10.1 (G), R22.1
unnamed: Q10.3 (D), R30.2
unnamed: Q11.1 (G), R23.1
unnamed: Q11.3 (D), R31.2
unnamed: Q12.1 (G), R24.1
unnamed: Q12.3 (D), R32.2
unnamed: Q15.4 (G), U2.31 (TG2)
unnamed: Q17.4 (G), U2.33 (BG2)
unnamed: Q18.1 (S), Q18.2 (S), Q18.3 (S), R176.1, R177.2
unnamed: Q18.4 (G), U2.21 (BGATE)
unnamed: R1.1, R58.1, U14.4 (EN)
unnamed: R2.1, U27.3 (FLG)
unnamed: R3.2, U2.8 (RT)
unnamed: R4.2, U4.35 (GPIO1)
unnamed: R5.2, U4.36 (GPIO2)
unnamed: R6.2, U4.34 (~WDTB)
unnamed: R8.2, U2.25 (ILIMIT)
unnamed: R9.2, U4.10 (C8)
unnamed: R10.2, U4.12 (C7)
unnamed: R11.2, U4.14 (C6)
unnamed: R12.2, U4.16 (C5)
unnamed: R13.2, U4.18 (C4)
unnamed: R14.2, U4.20 (C3)
unnamed: R15.2, U4.22 (C2)
unnamed: R16.2, U4.24 (C1)
unnamed: R17.2, U4.11 (S8)
unnamed: R18.2, U4.13 (S7)
unnamed: R19.2, U4.15 (S6)
unnamed: R20.2, U4.17 (S5)
unnamed: R21.2, U4.19 (S4)
unnamed: R22.2, U4.21 (S3)
unnamed: R23.2, U4.23 (S2)
unnamed: R24.2, U4.25 (S1)
unnamed: R34.1, R94.2, U2.9 (~SHDN)
unnamed: R35.2, U8.10 (OE), U28.5 (DIR)
unnamed: R36.2, U23.10 (IREF)
unnamed: R37.2, U23.2 (S0)
unnamed: R38.2, U23.3 (S1)
unnamed: R39.2, U23.4 (S2)
unnamed: R40.2, U23.7 (~PD)
unnamed: R51.2, U2.14 (TIMER)
unnamed: R59.1, U9.78 (USB_R1)
unnamed: R59.2, U9.79 (USB_R1RTN)
unnamed: R60.2, R62.1, U9.73 (USB_VBUS)
unnamed: R63.2, U9.35 (SDA/SMBDAT)
unnamed: R64.2, U10.32 (HPD)
unnamed: R77.2, U10.51 (REFCLK)
unnamed: R78.1, U4.30 (Vtemp2)
unnamed: R79.1, R86.1, U4.29 (Vtemp1)
unnamed: R80.2, U2.28 (VC)
unnamed: R81.1, U9.33 (GRSTz)
unnamed: R83.1, U24.3 (FLG)
unnamed: R84.1, U9.39 (PWRON0z_BATEN0)
unnamed: R85.2, U9.40 (OVERCUR0z)
unnamed: R111.2, U1.118 (USB1_VBUS)
unnamed: R112.2, R136.2, U3.18 (SDIN)
unnamed: R113.1, SW3.1
unnamed: R114.2, U3.12 (BCLK)
unnamed: R121.2, U3.14 (DACDAT)
unnamed: R122.2, U23.8 (OE)
unnamed: R129.1, R131.1, U10.15 (SCL)
unnamed: R130.1, R132.1, U10.16 (SDA)
unnamed: R66.2, R135.2, U3.17 (SCLK)
unnamed: R137.2, U5.7 (~INT1/CLKOUT)
unnamed: R138.1, U3.11 (MCLK)
unnamed: R139.2, U3.15 (ADCLRC)
unnamed: R141.2, U3.2 (LINPUT3)
unnamed: R150.2, U3.16 (ADCDAT)
unnamed: R151.2, U3.13 (DACLRC)
unnamed: R154.2, U1.30 (UART3_TXD)
unnamed: R155.1, U1.32 (UART3_RXD)
unnamed: R160.2, U11.20 (~W_DISABLE)
unnamed: R161.2, U22.2 (LV_SUPPLY)
unnamed: R173.1, R174.2, U2.17 (VFB)
unnamed: R54.1, R174.1, U2.18 (FBG)
unnamed: R182.1, U2.19 (VFBMIN)
unnamed: R54.2, R56.2, R182.2, U2.26 (VFBMAX)
unnamed: R185.2, R188.1, U13.1 (EN)
unnamed: R186.2, R189.1, U19.1 (EN)
unnamed: R193.2, U2.11 (MODE)
unnamed: R196.1, U20.3 (FLG)
unnamed: TP1.1, U1.180 (SAI3_MCLK/PWM4)
unnamed: TP2.1, U1.35 (USB1_OTG_ID)
unnamed: TP8.1, U1.8 (PMIC_ON_REQ)
unnamed: TP10.1, U1.143 (GP_M4_NMI)
unnamed: TP12.1, U1.174 (SAI2_RXC)
unnamed: U5.1 (OSCI), Y4.1
unnamed: U5.2 (OSCO), Y4.2
PCIE1_CLK_N: R148.2, U1.60 (PCIE1_REFCLK_N), U11.11 (RefClk-)
PCIE1_CLK_P: R123.2, U1.58 (PCIE1_REFCLK_P), U11.13 (RefClk+)
PCIE1_PWR_EN: R186.1, U18.9 (PIO0_20), U20.4 (EN)
PCIE1_RESETn: U1.37 (PCIE_RST_B), U11.22 (~PERST)
PCIE1_RX_N: U1.54 (PCIE1_RX_N), U11.23 (PERn0)
PCIE1_RX_P: U1.52 (PCIE1_RX_P), U11.25 (PERp0)
PCIE1_TX_N: U1.48 (PCIE1_TX_N), U11.31 (PETn0)
PCIE1_TX_P: U1.46 (PCIE1_TX_P), U11.33 (PETp0)
PCIE2_CLK_N: U1.66 (PCIE2_REFCLK_N), U23.11 (CLKD_N)
PCIE2_CLK_P: U1.64 (PCIE2_REFCLK_P), U23.12 (CLKD_P)
PCIE2_RESETn: J10.50, U1.24 (WIFI_RESET)
PCIE2_RX_N: J10.41, U1.78 (PCIE2_RX_N)
PCIE2_RX_P: J10.43, U1.76 (PCIE2_RX_P)
PCIE2_TX_N: J10.47, U1.72 (PCIE2_TX_N)
PCIE2_TX_P: J10.49, U1.70 (PCIE2_TX_P)
SD2_CD: J3.10 (CARD_DETECT), R42.2, U1.26 (SD2_CD)
SD2_CLK: U1.22 (SD2_CLK), U28.3 (A)
SD2_CMD: U1.20 (SD2_CMD), U8.7 (A6)
SD2_DATA0: U1.12 (SD2_DATA0), U8.3 (A2)
SD2_DATA1: U1.14 (SD2_DATA1), U8.1 (A1)
SD2_DATA2: U1.16 (SD2_DATA2), U8.9 (A8)
SD2_DATA3: U1.18 (SD2_DATA3), U8.8 (A7)
SPK_PWR: F3.1, R111.1, R152.1, U24.1 (OUT)
USB1_DN: U1.100 (USB1_D_N), U9.69 (USB_DM_UP)
USB1_DP: U1.102 (USB1_D_P), U9.70 (USB_DP_UP)
USB1_RX_N: U1.112 (USB1_RX_N), U9.62 (USB_SSTXM_UP)
USB1_RX_P: U1.114 (USB1_RX_P), U9.63 (USB_SSTXP_UP)
USB1_TX_N: U1.106 (USB1_TX_N), U9.65 (USB_SSRXM_UP)
USB1_TX_P: U1.108 (USB1_TX_P), U9.66 (USB_SSRXP_UP)
USB2_DN: J17.2 (D-), U1.125 (USB2_D_N), U21.3, U21.12
USB2_DP: J17.3 (D+), U1.127 (USB2_D_P), U21.4, U21.11
USB2_RX_N: J17.5 (SSRX-), U1.121 (USB2_RX_N), U21.7, U21.8
USB2_RX_P: J17.6 (SSRX+), U1.119 (USB2_RX_P), U21.6, U21.9
USB2_TX_N: J17.8 (SSTX-), U1.115 (USB2_TX_N), U21.2, U21.13
USB2_TX_P: J17.9 (SSTX+), U1.113 (USB2_TX_P), U21.1, U21.14
USB3_1_DN: J6.2 (D-), U9.3 (USB_DM_DN0), U25.3, U25.12
USB3_1_DP: J6.3 (D+), U9.2 (USB_DP_DN0), U25.4, U25.11
USB3_1_SSRXN: J6.5 (SSRX-), U9.7 (USB_SSRXM_DN0), U25.7, U25.8
USB3_1_SSRXP: J6.6 (SSRX+), U9.6 (USB_SSRXP_DN0), U25.6, U25.9
USB3_1_SSTXN: C40.1, U9.9 (USB_SSTXM_DN0)
USB3_1_SSTXP: C42.1, U9.8 (USB_SSTXP_DN0)
USB3_2_DN: J5.2 (D-), U9.59 (USB_DM_DN1), U26.3, U26.12
USB3_2_DP: J5.3 (D+), U9.60 (USB_DP_DN1), U26.4, U26.11
USB3_2_SSRXN: J5.5 (SSRX-), U9.54 (USB_SSRXM_DN1), U26.7, U26.8
USB3_2_SSRXP: J5.6 (SSRX+), U9.53 (USB_SSRXP_DN1), U26.6, U26.9
USB3_2_SSTXN: C39.1, U9.56 (USB_SSTXM_DN1)
USB3_2_SSTXP: C41.1, U9.55 (USB_SSTXP_DN1)
USB3_3_DN: R92.1, U9.18 (USB_DM_DN2)
USB3_3_DP: R90.1, U9.17 (USB_DP_DN2)
USB3_3_SSRXN: J12.9, U9.13 (USB_SSRXM_DN2)
USB3_3_SSRXP: J12.7, U9.12 (USB_SSRXP_DN2)
USB3_3_SSTXN: J12.5, U9.15 (USB_SSTXM_DN2)
USB3_3_SSTXP: J12.3, U9.14 (USB_SSTXP_DN2)
USB3_4_DN: R93.1, U9.44 (USB_DM_DN3)
USB3_4_DP: R91.1, U9.45 (USB_DP_DN3)
USB3_4_SSRXN: J12.10, U9.48 (USB_SSRXM_DN3)
USB3_4_SSRXP: J12.8, U9.47 (USB_SSRXP_DN3)
USB3_4_SSTXN: J12.6, U9.50 (USB_SSTXM_DN3)
USB3_4_SSTXP: J12.4, U9.49 (USB_SSTXP_DN3)
USBH_1V1: C9.1, C11.1, C12.1, C13.1, C15.1, C21.1, C66.1, C86.1, C88.1, C90.1, C91.1, C92.1, FB2.2, U9.1 (VDD11), U9.5 (VDD11), U9.10 (VDD11), U9.11 (VDD11), U9.16 (VDD11), U9.20 (VDD11), U9.26 (VDD11), U9.32 (VDD11), U9.37 (VDD11), U9.42 (VDD11), U9.46 (VDD11), U9.51 (VDD11), U9.52 (VDD11), U9.57 (VDD11), U9.61 (VDD11), U9.67 (VDD11), U9.71 (VDD11)
USBH_3V3: C14.1, C20.1, C43.1, C73.1, C87.1, C89.1, FB1.2, R63.1, R85.1, U9.4 (VDD33), U9.19 (VDD33), U9.21 (VDD33), U9.38 (VDD33), U9.43 (VDD33), U9.58 (VDD33), U9.68 (VDD33), U9.72 (VDD33), U9.77 (VDD33), U9.80 (VDD33)
USB_PWR: D14.2 (A), F3.2, FB5.1, FB6.1, FB7.1, FB8.1, FB9.1, FB15.1, J12.11, J12.12, J12.13, J12.14, R7.2, R60.1
USB_PWR_EN: U18.25 (PIO1_31), U24.4 (EN)
USB_RESETn: R81.2, R103.2, U1.131 (USB_HUB_RESET)

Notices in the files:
README.md:
License: source-available
web/boards/mnt-reform-motherboard.kicad_pcb:
License: CERN-OHL-S 2.0
